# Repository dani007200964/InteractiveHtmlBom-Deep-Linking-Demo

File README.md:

# Interactive HTML BOM Linking Demo

This project was created to demonstrate the linking capabilities of the [Interactive HTML BOM](https://github.com/openscopeproject/interactivehtmlbom).

The __live demo__ found here: https://dani007200964.github.io/InteractiveHtmlBom-Deep-Linking-Demo/

## Usage

You can create URL liks to __components__ and __nets__ like this:
- Link to __R1__: `ibom.html?ref=R1` -> [link](https://dani007200964.github.io/InteractiveHtmlBom-Deep-Linking-Demo/?ref=R1&id=1)
- Link to __VCC__: `ibom.html?net=VCC` -> [link](https://dani007200964.github.io/InteractiveHtmlBom-Deep-Linking-Demo/?net=VCC)

Because html rules there are some specia characters, like `+` or `-` symbols and so on. It is really a pain, because PCB designs often has these characters( `+3V3`, `-5V` and so on... ). For this reason some URL woodoo is needed to 'escape' these characters. For this reason a copy link button added next to each net and component name, that makes things simple.

# Designator error handling

KiCad assigns a unique identifier to every component placed on the PCB. This identifier can be used to reference a component even if its designator changes. As a result, components can be identified not only by their designator but also by their unique ID.

Unfortunately, unique IDs are usually not very descriptive ( most of the time they are just numeric values ) making them less user-friendly for everyday reference. However, they provide an important advantage: __if the PCB design changes and a component receives a new designator, links can still remain valid across revisions.__

For this reason, generated component links include both the designator and the unique identifier. If a mismatch is detected between the two, a warning dialog is displayed in the top-right corner of the screen. The user can then choose whether to open the link using the designator or the unique identifier.

Example of a broken link: [D: R2 UID: R1](https://dani007200964.github.io/InteractiveHtmlBom-Deep-Linking-Demo/?ref=R2&id=1)

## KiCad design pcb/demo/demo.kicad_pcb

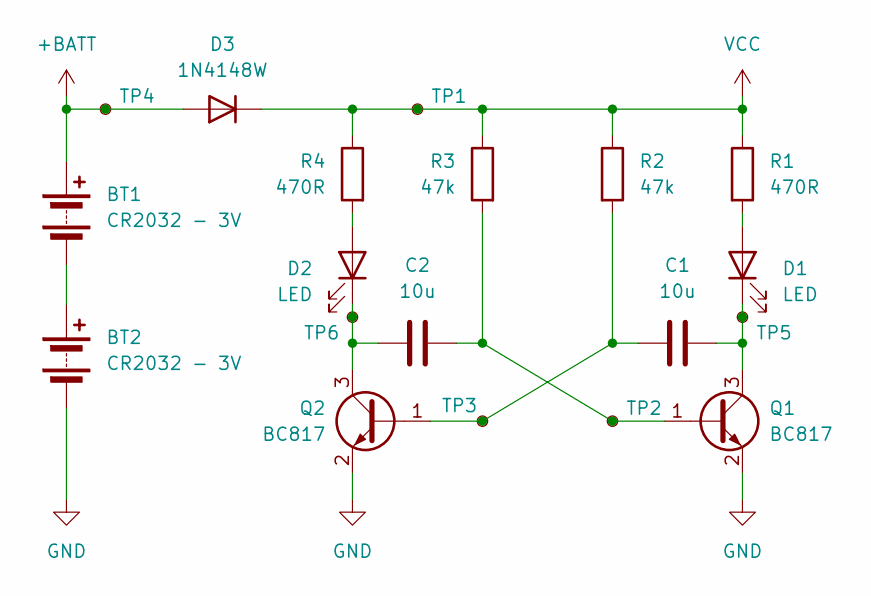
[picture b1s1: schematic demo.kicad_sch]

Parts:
BT1, BT2: CR2032 - 3V; BatteryHolder_Keystone_3002_1x2032
C1, C2: 10u; C_0805_2012Metric
D1, D2: LED; LED_0603_1608Metric_Pad1.05x0.95mm_HandSolder
D3: 1N4148W; D_SOD-123
Q1, Q2: BC817; SOT-23
R1, R4: 470R; R_0603_1608Metric_Pad0.98x0.95mm_HandSolder
R2, R3: 47k; R_0603_1608Metric_Pad0.98x0.95mm_HandSolder
TP1, TP2, TP3, TP4, TP5, TP6: TestPoint_Small; TestPoint_Pad_D2.0mm

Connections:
+BATT: BT1.1 (+), D3.2 (A), TP4.1 (1_1)
GND: BT2.2 (-), Q1.2 (E), Q2.2 (E)
unnamed: BT1.2 (-), BT2.1 (+)
unnamed: D1.2 (A), R1.2
unnamed: C1.2, D1.1 (K), Q1.3 (C), TP5.1 (1_1)
unnamed: D2.2 (A), R4.2
unnamed: C2.2, D2.1 (K), Q2.3 (C), TP6.1 (1_1)
unnamed: C2.1, Q1.1 (B), R3.2, TP2.1 (1_1)
unnamed: C1.1, Q2.1 (B), R2.2, TP3.1 (1_1)
VCC: D3.1 (K), R1.1, R2.1, R3.1, R4.1, TP1.1 (1_1)

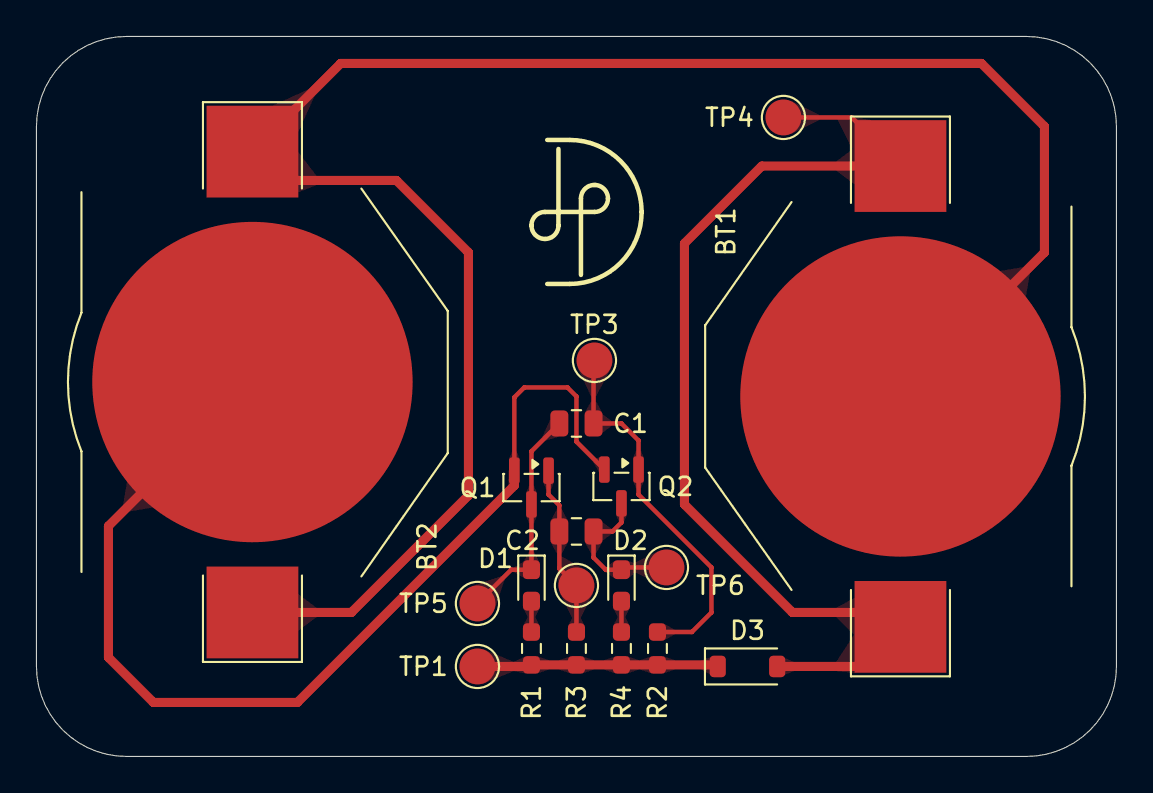
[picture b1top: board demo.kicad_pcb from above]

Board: 2 copper layers, 60.0 x 40.0 mm, 19 parts (0 on the bottom side), 10 nets.

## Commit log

2026-06-13 Working demo with compinent links
2026-06-13 index.html location fix for GitHub Pages
2026-06-21 Updated with the new linking system.
2026-06-21 Update README.md
    Description to the new features
